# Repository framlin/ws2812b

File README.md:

# ws2812b
experiments with neopixels

project, to make some experiments with Neopixels WS2812b

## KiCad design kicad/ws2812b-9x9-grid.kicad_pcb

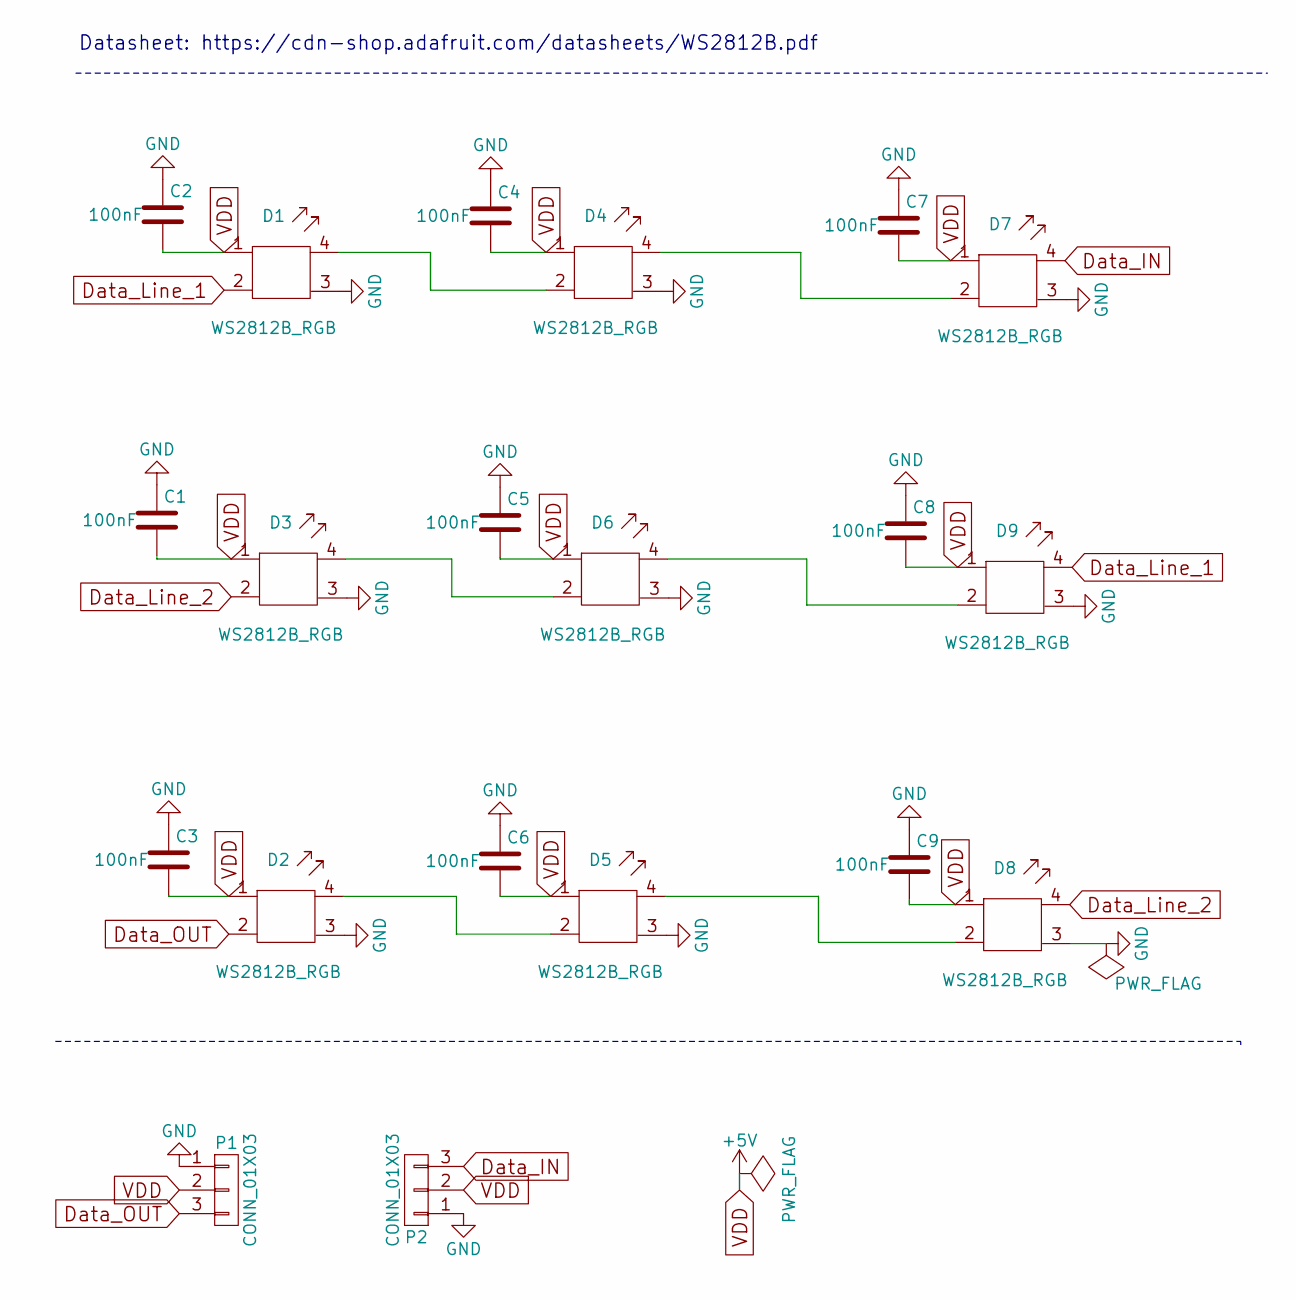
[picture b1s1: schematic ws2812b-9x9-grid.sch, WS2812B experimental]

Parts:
C1, C2, C3, C4, C5, C6, C7, C8, C9: 100nF; C_0805_HandSoldering
D1, D2, D3, D4, D5, D6, D7, D8, D9: WS2812B_RGB; WS2812B
P1, P2: CONN_01X03; PINHEAD1-3

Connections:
Data_IN: D7.4 (DIN), P2.3
Data_Line_1: D1.2 (DOUT), D9.4 (DIN)
Data_Line_2: D3.2 (DOUT), D8.4 (DIN)
Data_OUT: D2.2 (DOUT), P1.3
GND: C1.1, C2.1, C3.1, C4.1, C5.1, C6.1, C7.1, C8.1, C9.1, D1.3 (GND), D2.3 (GND), D3.3 (GND), D4.3 (GND), D5.3 (GND), D6.3 (GND), D7.3 (GND), D8.3 (GND), D9.3 (GND), P1.1, P2.1
unnamed: D1.4 (DIN), D4.2 (DOUT)
unnamed: D2.4 (DIN), D5.2 (DOUT)
unnamed: D3.4 (DIN), D6.2 (DOUT)
unnamed: D4.4 (DIN), D7.2 (DOUT)
unnamed: D5.4 (DIN), D8.2 (DOUT)
unnamed: D6.4 (DIN), D9.2 (DOUT)
VDD: C1.2, C2.2, C3.2, C4.2, C5.2, C6.2, C7.2, C8.2, C9.2, D1.1 (VDD), D2.1 (VDD), D3.1 (VDD), D4.1 (VDD), D5.1 (VDD), D6.1 (VDD), D7.1 (VDD), D8.1 (VDD), D9.1 (VDD), P1.2, P2.2

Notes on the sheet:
Datasheet: https://cdn-shop.adafruit.com/datasheets/WS2812B.pdf

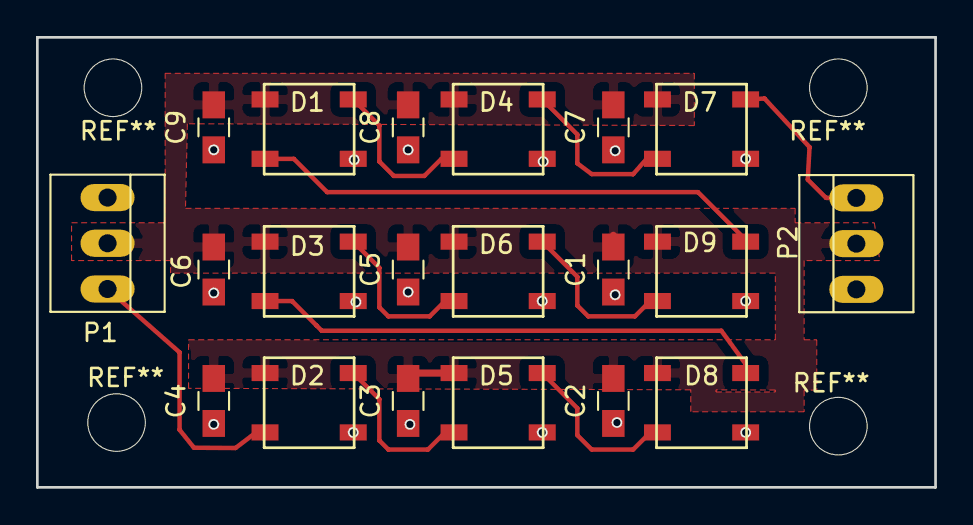
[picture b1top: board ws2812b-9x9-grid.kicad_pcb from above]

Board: 2 copper layers, 49.9 x 25.0 mm, 20 parts (0 on the bottom side), 12 nets.

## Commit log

2017-02-18 ws2812b-library, 9x9 matrix-schema
2017-02-18 experimental 9x9-grid board
2017-02-24 redo layout vdd and gnd planes
2017-02-24 cleanups
